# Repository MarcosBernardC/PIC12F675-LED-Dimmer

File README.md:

# PIC12F675 LED Dimmer

-green)

> **Nota:** Este proyecto ha sido migrado al **ARCHIVE**. Representa una base estable de control de potencia y gestión de recursos limitados en sistemas embebidos.

## 🚧 Avance Actual: Diseño de PCB y Modelado 3D
Actualmente, he finalizado el esquema lógico y la disposición de componentes principales. El siguiente paso es la integración de un módulo Buck Step-Down personalizado (LM2596) modelado en FreeCAD para mejorar la eficiencia térmica.

### Captura del Layout Preliminar
Aquí puedes ver la disposición actual de los transistores 2N2222A y los conectores JST para las 5 salidas LED.

---

## 📝 Descripción
Controlador de intensidad (Dimmer) de 5 canales para tiras LED de 12V, basado en el microcontrolador PIC12F675. 

* **Control:** PWM generado por software.
* **Potencia:** Transistores 2N2222A en configuración de conmutación.
* **Eficiencia:** Integración de regulador Buck LM2596 para reducir de 12V a 5V sin generar calor excesivo.

### 📂 Documentación de Hardware
Para una revisión detallada de las conexiones, consulta el <a href="https://raw.githubusercontent.com/MarcosBernardC/PIC12F675-LED-Dimmer/main/hardware/pic12f675-led-dimmer/pic12f675-led-dimmer.pdf" 
   target="_blank" 
   rel="noopener noreferrer">
   📄 <strong>Diagrama Técnico (PDF)</strong>
</a>

---

## 🧠 Firmware
El núcleo del sistema está escrito en **C** y optimizado para el PIC12F675 utilizando el compilador **XC8**.

* **Arquitectura:** Basada en interrupciones para una gestión eficiente del PWM.
* **Módulos clave:**  
    * Gestión de 5 canales de salida mediante conmutación rápida.
    * Configuración de registros internos (Oscilador, GPIO, Timers).

* **Código Fuente:** <a href="https://raw.githubusercontent.com/MarcosBernardC/PIC12F675-LED-Dimmer/main/src/main.c" target="_blank">📄 main.c (Vista Raw)</a>

---

## 🛠️ Herramientas utilizadas
* **Firmware:** C (XC8 Compiler), MPLAB X.
* **Diseño PCB:** KiCad 8.0.
* **Modelado 3D:** FreeCAD (integración paramétrica).
* **Automatización:** `Makefile` para compilación y gestión de assets.
* **Documentación:** LaTeX para el reporte de investigación.

---

## 📁 Estructura del Proyecto
* `/src`: Código fuente en C y artefactos de compilación (`.hex`).
* `/hardware`: Archivos de diseño de KiCad 8.0 y exportaciones PDF.
* `/docs`: Datasheets e investigación técnica detallada en LaTeX.
* `/simulation`: Archivos de simulación para validación lógica previa.
* `Makefile`: Automatización de la compilación del firmware.

---

## 🚀 Compilación y Uso
El proyecto utiliza un `Makefile` para automatizar las tareas:
* `make`: Compila el código fuente y genera el `.hex`.
* `make clean`: Limpia los archivos temporales de compilación.

---

## ✅ Resultados y Pruebas
El sistema ha sido validado físicamente con los siguientes resultados:
* **Estabilidad Térmica:** El regulador Buck LM2596 mantiene una temperatura operativa estable bajo carga completa (5 tiras LED).
* **Respuesta PWM:** Conmutación limpia sin parpadeo perceptible, optimizada mediante la gestión de registros del Timer0.
* **Integración Mecánica:** El modelo 3D de FreeCAD permitió un ensamble preciso dentro de la carcasa final.

## 📜 Licencia y Autoría
Este proyecto fue desarrollado íntegramente por **Marcos Bernard Calixto**.
* **Copyright:** © 2026 - No License Granted - All Rights Reserved.

---
© 2026 MB

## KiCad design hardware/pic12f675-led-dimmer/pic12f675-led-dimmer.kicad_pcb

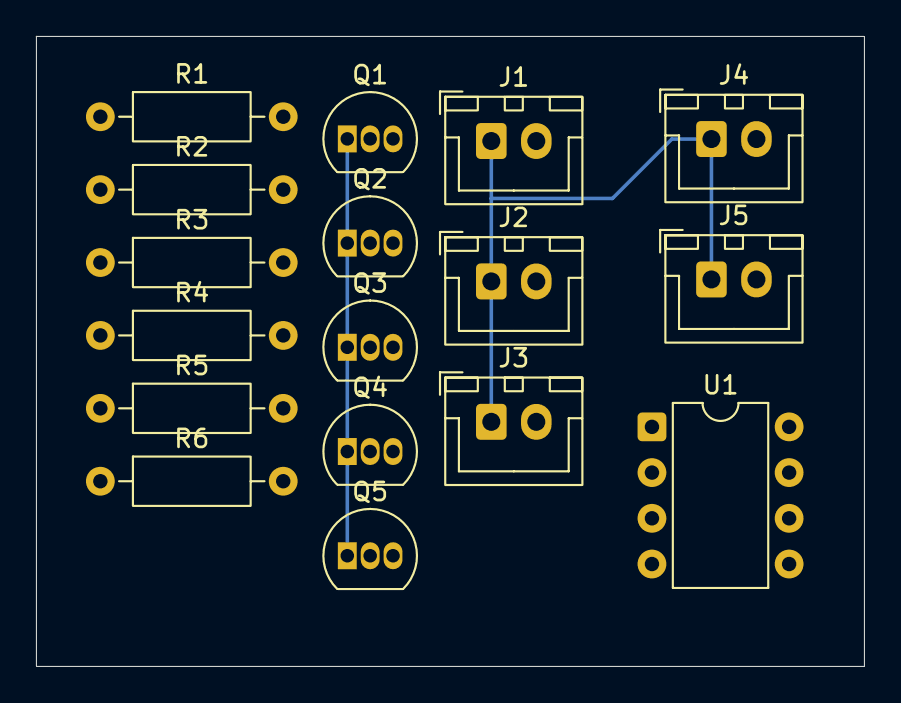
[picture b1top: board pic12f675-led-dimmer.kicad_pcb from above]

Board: 2 copper layers, 46.0 x 35.0 mm, 17 parts (0 on the bottom side), 8 nets.

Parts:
J1, J2, J3, J4, J5: Conn_01x02_Pin; JST_XH_B2B-XH-A_1x02_P2.50mm_Vertical
Q1, Q2, Q3, Q4, Q5: Q_NPN; TO-92_Inline
R1, R2, R3, R4, R5, R6: 1k; R_Axial_DIN0207_L6.3mm_D2.5mm_P10.16mm_Horizontal
U1: PIC12F675-xP; DIP-8_W7.62mm

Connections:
+5V: R1.2, U1.1 (VDD)
+12V: J1.1, J2.1, J3.1, J4.1, J5.1
unnamed: R2.1, U1.7 (GP0)
unnamed: R3.1, U1.6 (GP1)
unnamed: R4.1, U1.5 (GP2)
unnamed: R1.1, U1.4 (GP3)
unnamed: R5.1, U1.3 (GP4)
unnamed: R6.1, U1.2 (GP5)

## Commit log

2026-02-18 build: configurar entorno de documentacion con latexmk y estructura inicial
2026-02-18 feat: integrar simulación y estabilizar entorno de desarrollo para PIC12F675
    Este commit consolida el flujo de trabajo del proyecto:
    - Se añade el circuito de simulación profesional para SimulIDE.
    - Se integra la documentación técnica detallada en formato PDF.
    - Se estabiliza el entorno de compilación mediante el uso de XC8 v2.40 para compatibilidad nativa de arquitectura.
    - Se optimiza el archivo .gitignore para filtrar archivos temporales y de depuración de Microchip, manteniendo limpio el directorio de fuentes.
2026-02-18 build: optimizar flujo de LaTeX y limpieza de espacio de trabajo
    Se actualiza el Makefile para redirigir archivos auxiliares a docs/build y se limpia el .gitignore para mantener el directorio src libre de residuos de compilación.
2026-02-18 build: unificar flujo de trabajo y aislar directorios de construcción
    Este commit introduce mejoras significativas en la gestión del proyecto:
    - Se actualiza el Makefile para manejar de forma independiente la compilación de firmware (XC8) y documentación (LaTeX).
    - Se implementa el uso de directorios /build temporales para evitar la dispersión de archivos auxiliares en src/ y docs/.
    - Se automatiza la extracción de los binarios finales (.hex y .pdf) a sus respectivos directorios raíz.
    - Se añade la regla 'flash' para simplificar el proceso de grabación con PICkit 2.
2026-02-18 feat: ignorando directorio VideoEdit/. Firmware subido al PIC. Etapa 0 finalizada, led parpadeando con periodo de 500ms
2026-02-18 checkpoint: versión base lista para empezar con el juego de luces
2026-02-18 feat: implementar efecto ola para la base y probar en protoboard. TODO: implementar efecto para arco
2026-02-19 feat: implementar efecto ola base+arco en PIC12F675
    - Agregar fuses completos (CP=OFF, CPD=OFF, BOREN=ON) que bloqueaban el chip
    - Migrar arquitectura a timers por interrupciones (Timer0 PWM, Timer1 fade)
    - Base (GP0/GP1): contrafase suave, ciclo ~3s
    - Arco (GP2/GP4): contrafase independiente, ciclo ~6s
    - Corregir desborde unsigned en lógica de fade
    - Actualizar Makefile: quitar -V5 de pk2cmd, agregar reglas burn/erase/dump
2026-02-24 docs: integrar diseño de hardware A5 bajo la marca Bernardperulabs
2026-02-24 feat(hw): asignar huellas y definir layout preliminar de la PCB
2026-02-25 refactor(hw): preparar espacio para integración de módulo buck step-down
2026-02-25 docs: estructurar README profesional y optimizar reglas de gitignore
2026-04-28 Change project status to 'Finalizado' and add results
    Updated project status and added results section.
2026-05-02 Update copyright notice in README.md
    Removed 'BERNARDLAB.DEV' from copyright notice.
2026-05-02 Change project status note to ARCHIVE
    Updated project status note to reflect migration to the ARCHIVE.
2026-05-02 style(docs): maquillar enlaces de documentación técnica para mejor UX
2026-05-02 docs: implementar enlace técnico con apertura en nueva pestaña
2026-05-02 docs: actualizar enlace de código fuente a vista raw con apertura en pestaña nueva
2026-06-25 chore: actualizar activity a 'COMPLETED'
